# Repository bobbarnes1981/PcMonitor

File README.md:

DS18b20
    wired or connector?
    resistors on board?

pcb is 2.5" hdd size

arduino nano mount

leds?

display?

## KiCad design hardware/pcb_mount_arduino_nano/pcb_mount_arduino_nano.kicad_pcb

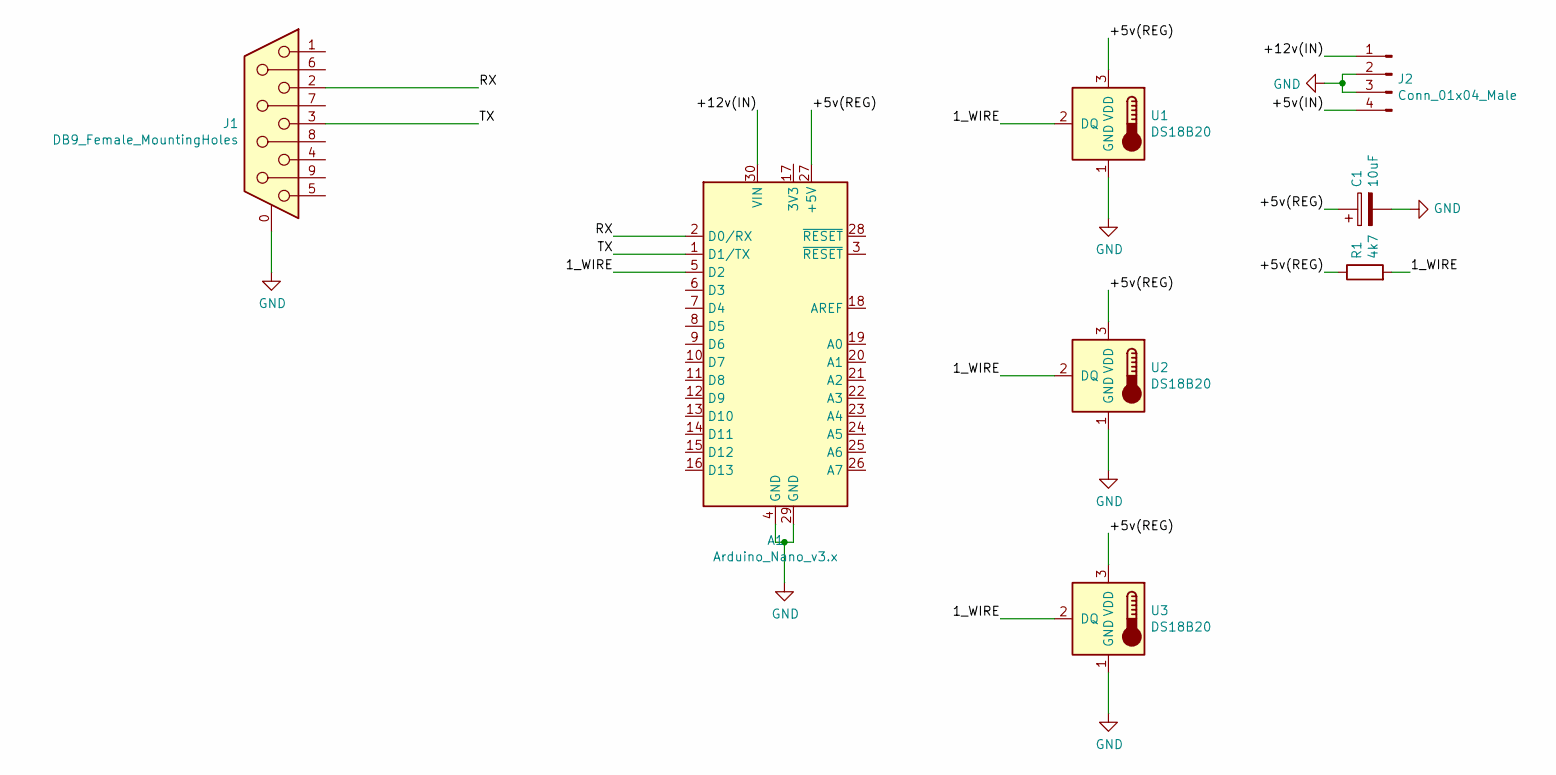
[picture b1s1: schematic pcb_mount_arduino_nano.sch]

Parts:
A1: Arduino_Nano_v3.x; Arduino_Nano
C1: 10uF; CP_Radial_D5.0mm_P2.00mm
J1: DB9_Female_MountingHoles; DSUB-9_Female_Vertical_P2.77x2.84mm_MountingHoles
J2: Conn_01x04_Male; TE_MATE-N-LOK_350211-1_1x04_P5.08mm_Vertical
R1: 4k7; R_Axial_DIN0207_L6.3mm_D2.5mm_P10.16mm_Horizontal
U1, U2, U3: DS18B20; TO-92_Inline

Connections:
/1_WIRE: A1.5 (D2), R1.2, U1.2 (DQ), U2.2 (DQ), U3.2 (DQ)
/+5v(IN): J2.4
/+5v(REG): A1.27 (+5V), C1.1, R1.1, U1.3 (VDD), U2.3 (VDD), U3.3 (VDD)
/+12v(IN): A1.30 (VIN), J2.1
/RX: A1.2 (D0/RX), J1.2
/TX: A1.1 (D1/TX), J1.3
GND: A1.4 (GND), A1.29 (GND), C1.2, J1.0 (PAD), J2.2, J2.3, U1.1 (GND), U2.1 (GND), U3.1 (GND)

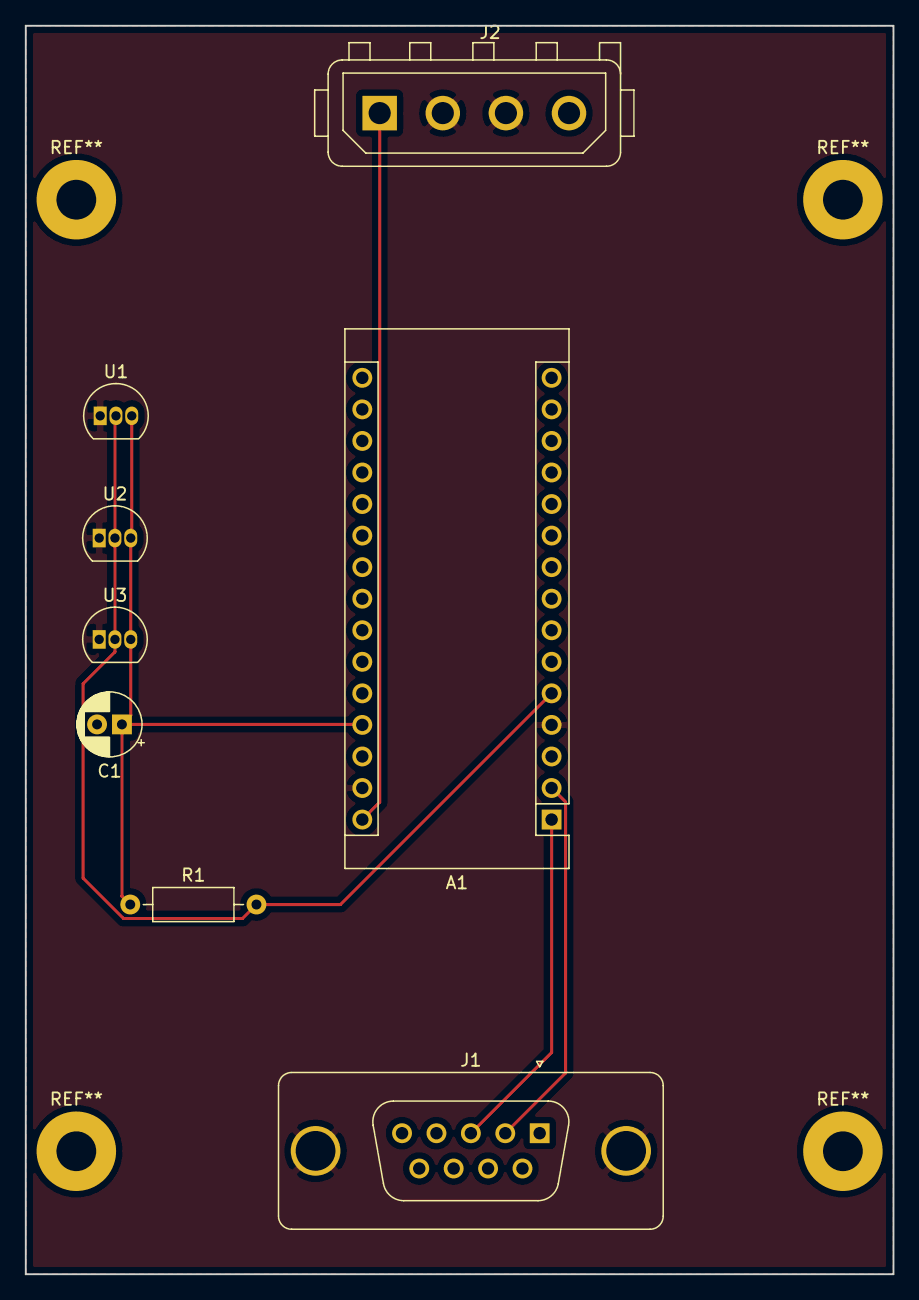
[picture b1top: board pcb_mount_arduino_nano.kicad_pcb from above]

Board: 2 copper layers, 69.8 x 100.5 mm, 8 parts (0 on the bottom side), 6 nets.

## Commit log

2020-09-08 Add firmware that outputs temperature over serial for DS18B20
2020-09-08 Add git ignore
2020-09-08 Add readme
2020-09-08 Add 2.5" drive sized pcb with arduino nano
2020-09-08 Add mounting holes and DS18B20
2020-09-08 Add serial port and power connector
2020-09-08 Convert graphic to edge cut
2020-09-08 Add render
2020-09-09 Add multiple 1 wire temperature sensors
2020-09-09 Add new render
